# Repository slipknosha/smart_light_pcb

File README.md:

# Smart Light PCB

KiCad hardware project for an ESP32-S3 BLE-controlled AC phase dimmer.

> [!WARNING]
> This project works with **220-230 VAC mains voltage**.
> Assembly, probing, flashing while connected to mains, and load testing require proper isolation, fusing, enclosure, and experience with high-voltage electronics.
> Treat this board as a prototype or lab project, not a certified consumer product.

## Related Repositories

The complete Smart Light project is split into two repositories:

- **PCB / KiCad hardware**: <https://github.com/slipknosha/smart_light_pcb/tree/develop>
- **ESP32-S3 firmware**: <https://github.com/slipknosha/smart_light/tree/develop>

This repository contains the schematic, PCB layout, BOM, 3D export, and manufacturing outputs.
The companion repository contains the ESP-IDF firmware that runs on this board.

## Project Overview

The board is a compact zero-cross synchronized triac dimmer built around an **ESP32-S3-WROOM-1** module.
It is designed to control a 220-230 VAC load using phase-angle dimming, with BLE control handled by firmware.

Main functional blocks:

- ESP32-S3 controller with native USB-C flashing
- Isolated AC/DC 5 V power supply based on Mean Well `IRM-05-5`
- 3.3 V logic rail generated by `LM1117MP-3.3`
- Zero-cross detector using `LTV-814`
- Random-phase optotriac driver using `MOC3052M`
- Main AC switching triac `BTB16-600B`
- BOOT and RESET buttons
- USB ESD protection and CC resistors
- AC input and load terminal blocks

## Firmware Compatibility

Use the firmware from:

<https://github.com/slipknosha/smart_light/tree/develop>

The current firmware expects this exact pin mapping:

| Board net | ESP32-S3 GPIO | Firmware module | Purpose |
|---|---:|---|---|
| `LTV_OUT` | `GPIO1` | `dimmer.c` | Zero-cross detector input |
| `MOC` | `GPIO2` | `dimmer.c` | Triac optodriver control output |
| `ESP_IO0` | `GPIO0` | Boot hardware | Bootloader button |
| `ESP_EN` | `EN` | Reset hardware | Reset / enable |
| `ESP_D-` | `USB_D-` / `GPIO19` | ESP-ROM / USB CDC | Native USB D- |
| `ESP_D+` | `USB_D+` / `GPIO20` | ESP-ROM / USB CDC | Native USB D+ |

The BLE device name is:

```text
SmartLight
```

The firmware exposes a custom BLE service and characteristic for dimming:

```text
Service:        7b5e0001-4c3f-4b3d-9a57-8d47b4ef0001
Characteristic: 7b5e0002-4c3f-4b3d-9a57-8d47b4ef0001
```

The characteristic accepts a binary little-endian unsigned integer in the range:

```text
0..100000
```

Typical nRF Connect writes:

```text
0      -> 00 00 00 00
1000   -> E8 03 00 00
10000  -> 10 27 00 00
50000  -> 50 C3 00 00
100000 -> A0 86 01 00
```

## Hardware Architecture

### Power Input and Rails

The board can receive 5 V from USB-C during development.
For standalone operation, the mains input feeds the isolated `IRM-05-5` AC/DC module.

Power chain:

```text
AC_L / AC_N -> IRM-05-5 -> 5 V -> LM1117MP-3.3 -> 3.3 V logic
```

The 5 V rail includes Schottky diode OR-ing/protection and decoupling capacitors.
The 3.3 V rail powers the ESP32-S3 and the low-voltage optocoupler side.

### Zero-Cross Detector

The zero-cross detector uses:

- `U1` - `LTV-814`
- `R1`, `R2` - 100 k mains-side resistors
- `R8` - 47 k pull-up on `LTV_OUT`

The isolated output is connected to `ESP32-S3 GPIO1` as `LTV_OUT`.
Firmware counts the accepted zero-cross edges and schedules the triac gate pulse relative to each half-cycle.

### Triac Driver

The triac gate path uses:

- `U3` - `MOC3052M` random-phase optotriac
- `Q2` - `BC847B` NPN transistor
- `R10` - 2.2 k base resistor
- `R11` - 100 k base pulldown
- `R3` - 180 ohm gate-side resistor
- `R12` - 330 ohm triac-side resistor
- `Q1` - `BTB16-600B` power triac

The ESP32 drives net `MOC` on `GPIO2`.
The firmware keeps this output low normally and sends a short pulse after each zero-cross delay.

### USB and Programming

The ESP32-S3 is wired for native USB flashing through `J3` USB-C.

USB-related parts:

- `J3` - USB-C receptacle
- `R4`, `R5` - 5.1 k CC resistors
- `U5` - `USBLC6-2SC6` ESD protection
- `SW2` - BOOT button on `ESP_IO0`
- `SW1` - RESET button on `ESP_EN`
- `J4` - 2x3 debug/programming header

The board can be flashed directly over USB without an external USB-UART converter.

## Connectors

| Connector | Label | Function |
|---|---|---|
| `J1` | `220V` | AC mains input, `AC_L` / `AC_N` |
| `J2` | `Load` | Switched AC load output |
| `J3` | USB-C | USB power and native ESP32-S3 flashing |
| `J4` | 2x3 header | `ESP_EN`, `TX`, `RX`, `ESP_IO0`, 3.3 V, GND |

## Key Components

| Reference | Part | Function |
|---|---|---|
| `U2` | `ESP32-S3-WROOM-1` | Main MCU / BLE controller |
| `PS1` | `IRM-05-5` | Isolated 5 V AC/DC supply |
| `U6` | `LM1117MP-3.3` | 3.3 V linear regulator |
| `U1` | `LTV-814` | Zero-cross optocoupler |
| `U3` | `MOC3052M` | Random-phase optotriac driver |
| `Q1` | `BTB16-600B` | Main AC triac |
| `Q2` | `BC847B` | MOC LED driver transistor |
| `U5` | `USBLC6-2SC6` | USB ESD protection |
| `F1` | Polyfuse | USB 5 V protection |

## Repository Structure

```text
smart_light_pcb/
├── README.md
├── LICENSE
├── sn.kicad_pro          # KiCad project
├── sn.kicad_sch          # schematic
├── sn.kicad_pcb          # PCB layout
├── sn.step               # exported 3D model
├── production/
│   ├── bom.csv           # bill of materials
│   ├── designators.csv
│   ├── netlist.ipc
│   ├── positions.csv     # pick-and-place
│   └── sn.zip            # Gerber + drill package
├── jlcpcb/
│   └── project.db
├── Snapeda.kicad_sym
├── Snapeda.pretty/
├── Snapeda.3dshapes/
└── sn-backups/
```

## Manufacturing Outputs

The `production/` directory contains files for fabrication and assembly:

- Gerber/drill archive: `production/sn.zip`
- BOM: `production/bom.csv`
- Pick-and-place: `production/positions.csv`
- IPC netlist: `production/netlist.ipc`
- Designator list: `production/designators.csv`

Review and regenerate these files after any schematic or PCB change before ordering.

## Suggested Bring-Up

1. Inspect the assembled PCB for shorts, solder bridges, and component orientation.
2. Power from USB only; verify 5 V and 3.3 V rails.
3. Confirm ESP32-S3 native USB flashing.
4. Flash the firmware from the companion repository.
5. Confirm BLE advertising as `SmartLight`.
6. Pair/bond from nRF Connect or the Android app.
7. Verify `LTV_OUT` zero-cross logs with mains connected under controlled conditions.
8. Test dimming with a suitable resistive load.
9. Move to real lamp testing only after the low-voltage and isolation checks pass.

## Safety Notes

- Keep the low-voltage USB/debug side isolated from mains during testing.
- Do not touch or probe the board while it is energized from AC.
- Use a safe enclosure and strain relief before any practical use.
- Check creepage/clearance and local electrical requirements before considering real deployment.
- The triac is non-isolated and may require thermal management depending on load current.

## License

This project is licensed under the **MIT License**.
See [LICENSE](LICENSE) for details.

## Author

**Vladyslav Bobrykov**

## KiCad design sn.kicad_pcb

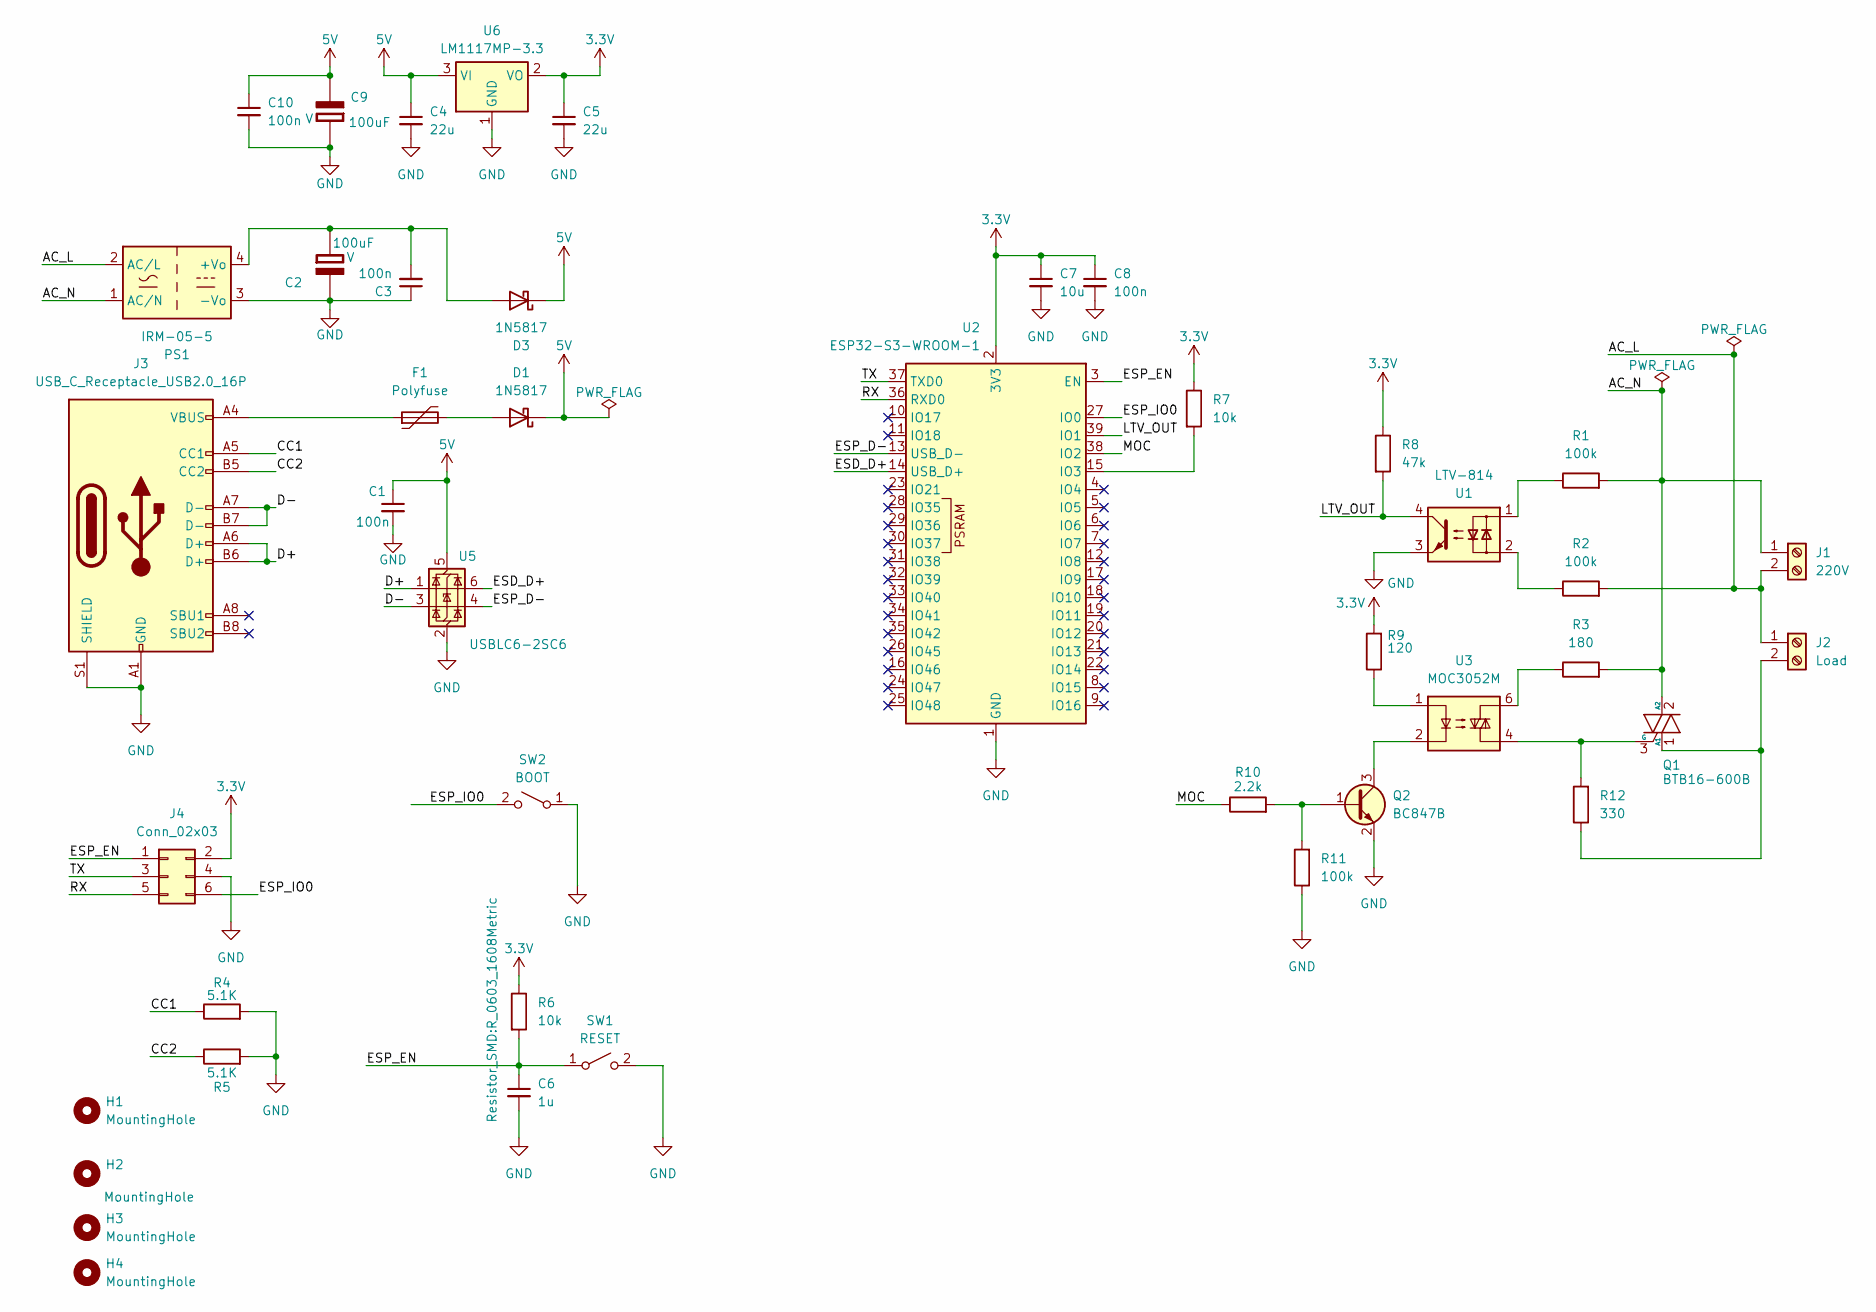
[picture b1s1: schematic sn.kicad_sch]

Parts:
C1, C3, C8, C10: 100n; C_0603_1608Metric
C2, C9: 100uF; CP_Elec_6.3x5.4; Rating V
C4, C5: 22u; C_0805_2012Metric
C6: 1u; C_0603_1608Metric
C7: 10u; C_0603_1608Metric
D1, D3: 1N5817; D_DO-41_SOD81_P10.16mm_Horizontal
F1: Polyfuse; Fuse_1206_3216Metric
H1, H2, H3, H4: MountingHole; MountingHole_3.2mm_M3
J1: 220V; TerminalBlock_Phoenix_MKDS-1,5-2_1x02_P5.00mm_Horizontal
J2: Load; TerminalBlock_Phoenix_MKDS-1,5-2_1x02_P5.00mm_Horizontal
J3: USB_C_Receptacle_USB2.0_16P; USB_C_Receptacle_GCT_USB4085
J4: Conn_02x03; Pins_2x03_2.54mm_TH; Part Number LL1009-2A, 2.54MM 2*3PIN HEADER,LENGTH=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
PS1: IRM-05-5; Converter_ACDC_MeanWell_IRM-05-xx_THT
Q1: BTB16-600B; TO-220-3_Vertical
Q2: BC847B; SOT-23
R1, R2: 100k; R_Axial_DIN0207_L6.3mm_D2.5mm_P10.16mm_Horizontal
R3: 180; R_Axial_DIN0207_L6.3mm_D2.5mm_P10.16mm_Horizontal
R4, R5: 5.1K; R_0603_1608Metric
R6, R7: 10k; R_0603_1608Metric
R8: 47k; R_0603_1608Metric
R9: 120; R_0603_1608Metric
R10: 2.2k; R_0603_1608Metric
R11: 100k; R_0603_1608Metric
R12: 330; R_Axial_DIN0207_L6.3mm_D2.5mm_P10.16mm_Horizontal
SW1: RESET; SW_Push_1P1T_NO_E-Switch_TL3301NxxxxxG
SW2: BOOT; SW_Push_1P1T_NO_E-Switch_TL3301NxxxxxG
U1: LTV-814; DIP-4_W7.62mm
U2: ESP32-S3-WROOM-1
U3: MOC3052M; DIP-6_W7.62mm
U5: USBLC6-2SC6; SOT-23-6
U6: LM1117MP-3.3; SOT-223-3_TabPin2

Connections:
3.3V: C5.1, C7.1, C8.1, J4.2 (+12V), R6.1, R7.1, R8.1, R9.2, U2.2 (3V3), U6.2 (VO)
5V: C1.1, C4.1, C9.2 (-), C10.1, D1.1 (K), D3.1 (K), U5.5 (VBUS), U6.3 (VI)
/AC_L: J1.2, J2.1, PS1.2 (AC/L), R2.2
/AC_N: J1.1, PS1.1 (AC/N), Q1.2 (A2), R1.2, R3.2
/CC1: J3.A5 (CC1), R4.1
/CC2: J3.B5 (CC2), R5.1
/D+: J3.A6 (D+), J3.B6 (D+), U5.1 (I/O1)
/D-: J3.A7 (D-), J3.B7 (D-), U5.3 (I/O2)
/ESD_D+: U2.14 (USB_D+), U5.6 (I/O1)
/ESP_D-: U2.13 (USB_D-), U5.4 (I/O2)
/ESP_EN: C6.1, J4.1 (+12V), R6.2, SW1.1 (A), U2.3 (EN)
/ESP_IO0: J4.6 (GND), SW2.2 (B), U2.27 (IO0)
/LTV_OUT: R8.2, U1.4, U2.39 (IO1)
/MOC: R10.1, U2.38 (IO2)
/RX: J4.5 (GND), U2.36 (RXD0)
/TX: J4.3 (GND), U2.37 (TXD0)
GND: C1.2, C2.2 (-), C3.1, C4.2, C5.2, C6.2, C7.2, C8.2, C9.1 (+), C10.2, J3.A1 (GND), J3.A12 (GND), J3.B1 (GND), J3.B12 (GND), J3.S1 (SHIELD), J4.4 (GND), PS1.3 (-Vo), Q2.2 (E), R4.2, R5.2, R11.1, SW1.2 (B), SW2.1 (A), U1.3, U2.1 (GND), U2.40 (GND), U2.41 (GND), U5.2 (GND), U6.1 (GND)
unnamed: C2.1 (+), C3.2, D3.2 (A), PS1.4 (+Vo)
unnamed: D1.2 (A), F1.2
unnamed: F1.1, J3.A4 (VBUS), J3.A9 (VBUS), J3.B4 (VBUS), J3.B9 (VBUS)
unnamed: J2.2, Q1.1 (A1), R12.1
unnamed: Q1.3 (G), R12.2, U3.4
unnamed: Q2.1 (B), R10.2, R11.2
unnamed: Q2.3 (C), U3.2
unnamed: R1.1, U1.1
unnamed: R2.1, U1.2
unnamed: R3.1, U3.6
unnamed: R9.1, U3.1
unnamed: R7.2, U2.15 (IO3)

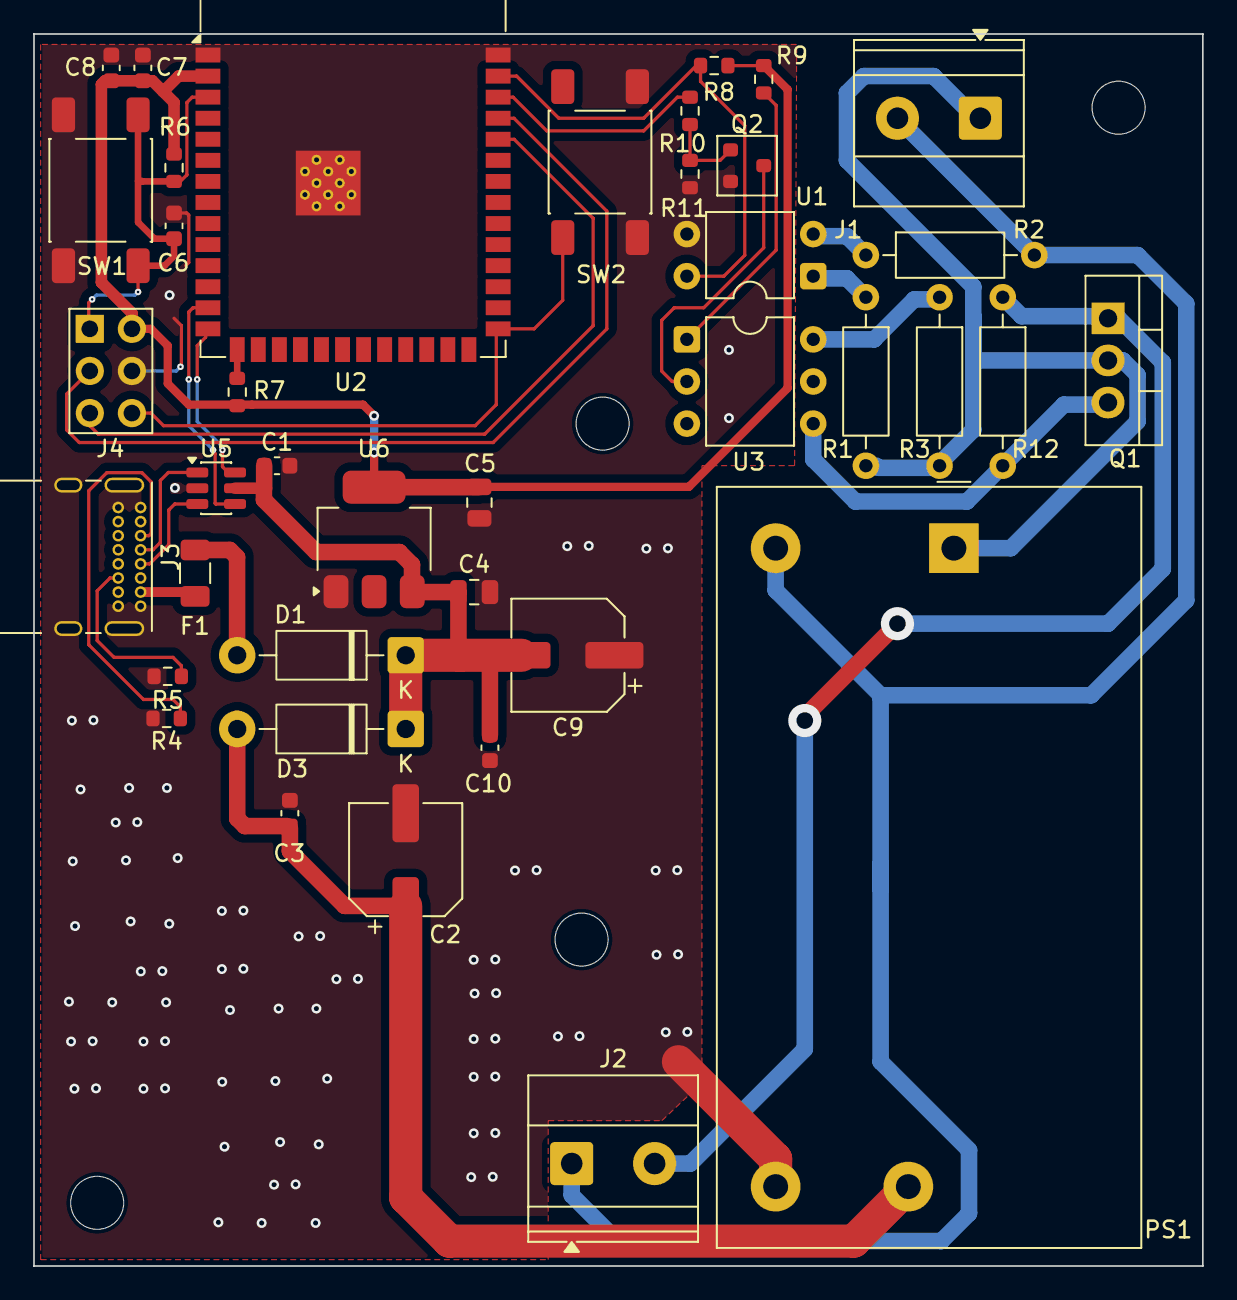
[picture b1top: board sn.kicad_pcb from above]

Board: 2 copper layers, 70.5 x 74.3 mm, 43 parts (0 on the bottom side), 29 nets.

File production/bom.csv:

Designator,Footprint,Quantity,Value,LCSC Part #
"C1, C10, C3, C8",0603,4,100n,C14663
C2,CP_Elec_6.3x5.4,1,100uF,C134801
"C4, C5",0805,2,22u,C45783
C6,0603,1,1u,C15849
C7,0603,1,10u,C19702
C9,CP_Elec_6.3x5.4,1,100uF,
"D1, D3",D_DO-41_SOD81_P10.16mm_Horizontal,2,1N5817,
"D2, D4",D_SOD-923,2,ESD3.3,
F1,1206,1,Polyfuse,
J1,"TerminalBlock_Phoenix_MKDS-1,5-2_1x02_P5.00mm_Horizontal",1,220V,
J2,"TerminalBlock_Phoenix_MKDS-1,5-2_1x02_P5.00mm_Horizontal",1,Load,
J3,USB_C_Receptacle_GCT_USB4085,1,USB_C_Receptacle_USB2.0_16P,
J4,Pins_2x03_2.54mm_TH,1,Conn_02x03,
"L1, L2",0603,2,220Ohm,
PS1,Converter_ACDC_MeanWell_IRM-05-xx_THT,1,IRM-05-5,
Q1,TO-220-3_Vertical,1,BTB16-600B,
Q2,SOT-23,1,BC847B,C57668
"R1, R2",R_Axial_DIN0207_L6.3mm_D2.5mm_P10.16mm_Horizontal,2,100k,
R10,0603,1,2.2k,C4190
R11,0603,1,100k,C25803
R12,R_Axial_DIN0207_L6.3mm_D2.5mm_P10.16mm_Horizontal,1,330,
R3,R_Axial_DIN0207_L6.3mm_D2.5mm_P10.16mm_Horizontal,1,180,
"R4, R5",0603,2,5.1K,C23186
"R6, R7",0603,2,10k,C25804
R8,0603,1,47k,C25819
R9,0603,1,120,C22787
SW1,SW_Push_1P1T_NO_E-Switch_TL3301NxxxxxG,1,RESET,
SW2,SW_Push_1P1T_NO_E-Switch_TL3301NxxxxxG,1,BOOT,
U1,DIP-4_W7.62mm,1,LTV-814,
U2,ESP32-S3-WROOM-1,1,ESP32-S3-WROOM-1,C2913198
U3,DIP-6_W7.62mm,1,MOC3052M,
U5,SOT-23-6,1,USBLC6-2SC6,C7519
U6,SOT-223-3_TabPin2,1,LM1117MP-3.3,C3750685

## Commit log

2026-04-07 add desing of PCB of AC dimmer
2026-04-08 redesing pcb
2026-04-13 add ASM
2026-04-13 remove l1 l2 d4 d2
2026-04-13 return tht type-c
2026-04-14 fix according review from JLCPCB
2026-04-14 write readme.md
